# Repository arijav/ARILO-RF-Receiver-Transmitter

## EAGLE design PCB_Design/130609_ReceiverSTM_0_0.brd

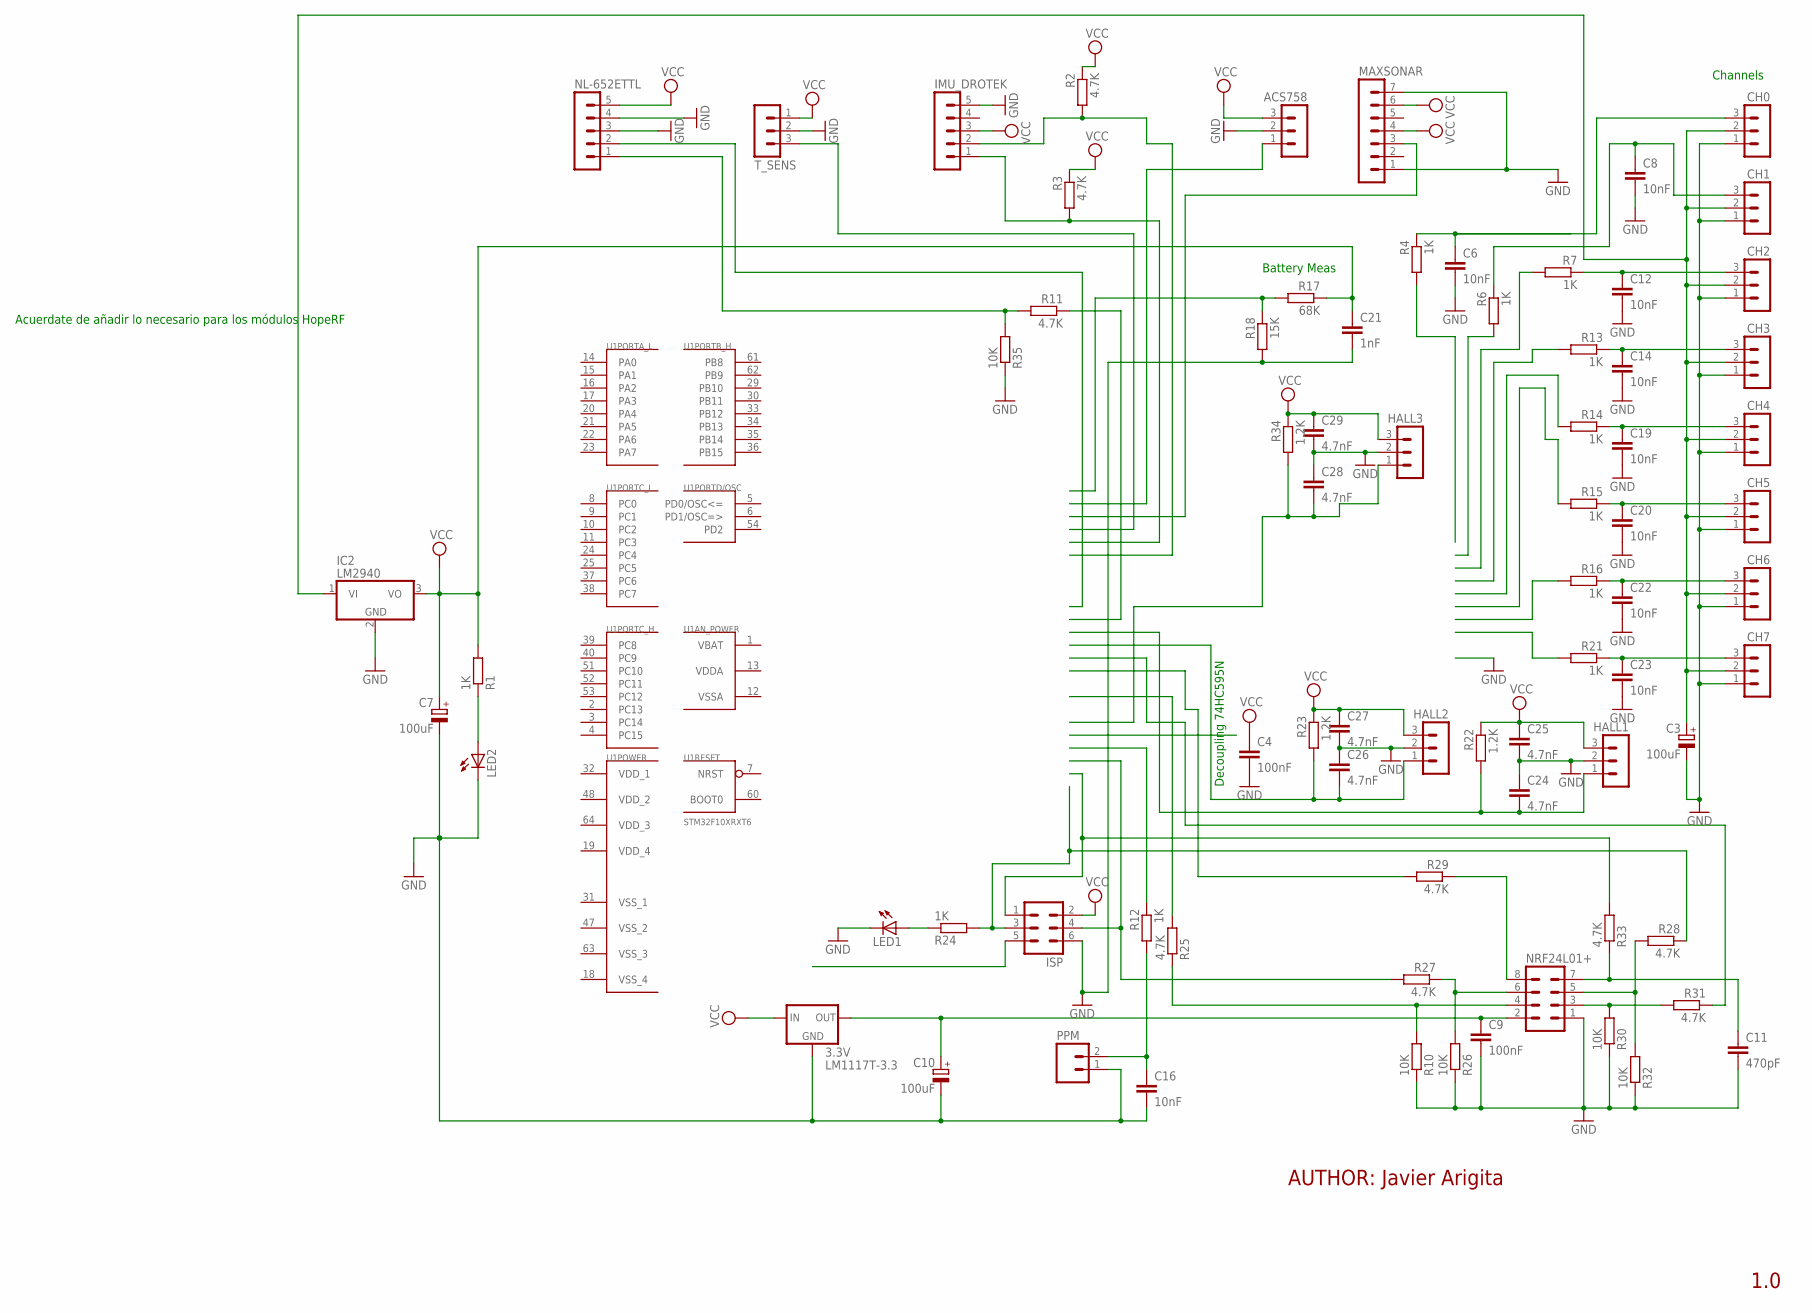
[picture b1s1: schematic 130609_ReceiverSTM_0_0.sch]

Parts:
3.3V: LM1117T-3.3; TO220
ACS758: MA03-1
C3, C7, C10: 100uF; E2,5-6E
C4, C9: 100nF; C050-025X075
C6, C8, C12, C14, C16, C19, C20, C22, C23: 10nF; C025-030X050
C11: 470pF; C025-030X050
C21: 1nF; C050-025X075
C24, C25, C26, C27, C28, C29: 4.7nF; C025-030X050
CH0, CH1, CH2, CH3, CH4, CH5, CH6, CH7: MA03-1
HALL1, HALL2, HALL3: MA03-1
IC2: LM2940; TO220V
IMU_DROTEK: MA05-1
ISP: MA03-2
LED1, LED2: LED5MM
MAXSONAR: MA07-1
NL-652ETTL: MA05-1
NRF24L01+: MA04-2
PPM: M02; 02P
R1, R4, R6, R7, R12, R13, R14, R15, R16, R21, R24: 1K; 0204/7
R2, R3, R11, R25, R27, R28, R29, R31, R33: 4.7K; 0204/7
R10, R26, R30, R32, R35: 10K; 0204/7
R17: 68K; 0204/7
R18: 15K; 0204/7
R22, R23, R34: 1.2K; 0204/7
T_SENS: MA03-1
U1: STM32F10XRXT6; TQFP64

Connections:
GND: 3.3V.1 (GND), ACS758.2, C3.-, C4.2, C6.2, C7.-, C8.2, C9.2, C10.-, C11.2, C12.2, C14.2, C16.2, C19.2, C20.2, C21.2, C22.2, C23.2, C24.1, C25.2, C26.1, C27.2, C28.1, C29.2, CH0.1, CH1.1, CH2.1, CH3.1, CH4.1, CH5.1, CH6.1, CH7.1, HALL1.2, HALL2.2, HALL3.2, IC2.2 (GND), IMU_DROTEK.5, ISP.6, LED1.K (C), LED2.K (C), MAXSONAR.1, MAXSONAR.7, NL-652ETTL.3, NL-652ETTL.4, NRF24L01+.1, PPM.1, R10.1, R18.2, R26.1, R30.1, R32.1, R35.1, T_SENS.2
MAX_BRIDGE: NL-652ETTL.2
unnamed: 3.3V.3 (IN), ACS758.3, C4.1, C7.+, C21.1, C25.1, C27.1, C29.1, HALL1.3, HALL2.3, HALL3.3, IC2.3 (VO), IMU_DROTEK.3, ISP.2, MAXSONAR.4, MAXSONAR.6, NL-652ETTL.5, R1.2, R2.1, R3.1, R17.1, R22.1, R23.1, R34.1, T_SENS.1
unnamed: LED2.A, R1.1
unnamed: IMU_DROTEK.2, R2.2
unnamed: C28.2, HALL3.1, R34.2
unnamed: C24.2, HALL1.1, R22.2
unnamed: 3.3V.2 (OUT), C9.1, C10.+, NRF24L01+.2
unnamed: NRF24L01+.4, R10.2, R25.1
unnamed: NRF24L01+.3, R30.2, R31.2
unnamed: C16.1, PPM.2, R12.2
unnamed: NL-652ETTL.1, R11.2, R35.2
unnamed: IMU_DROTEK.1, R3.2
unnamed: C26.2, HALL2.1, R23.2
unnamed: R17.2, R18.1
unnamed: C3.+, CH0.2, CH1.2, CH2.2, CH3.2, CH4.2, CH5.2, CH6.2, CH7.2, IC2.1 (VI)
unnamed: ISP.3, R24.2, R28.1
unnamed: LED1.A, R24.1
unnamed: ISP.1, R33.2
unnamed: ISP.4, R27.2
unnamed: NRF24L01+.8, R29.1
unnamed: NRF24L01+.6, R26.2, R27.1
unnamed: NRF24L01+.5, R28.2, R32.2
unnamed: C11.1, NRF24L01+.7, R33.1
unnamed: C6.1, CH0.3, R4.1
unnamed: C8.1, CH1.3, R6.1
unnamed: C12.1, CH2.3, R7.1
unnamed: C14.1, CH3.3, R13.1
unnamed: C19.1, CH4.3, R14.1
unnamed: C20.1, CH5.3, R15.1
unnamed: C22.1, CH6.3, R16.1
unnamed: C23.1, CH7.3, R21.1
VBAT: U1.1 (VBAT)
VDDA: U1.13 (VDDA)
VDD_1: U1.32 (VDD_1)
VDD_2: U1.48 (VDD_2)
VDD_3: U1.64 (VDD_3)
VDD_4: U1.19 (VDD_4)
VSSA: U1.12 (VSSA)
VSS_1: U1.31 (VSS_1)
VSS_2: U1.47 (VSS_2)
VSS_3: U1.63 (VSS_3)
VSS_4: U1.18 (VSS_4)

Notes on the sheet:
Battery Meas
Acuerdate de añadir lo necesario para los módulos HopeRF
AUTHOR: Javier Arigita
1.0
Channels
Decoupling 74HC595N

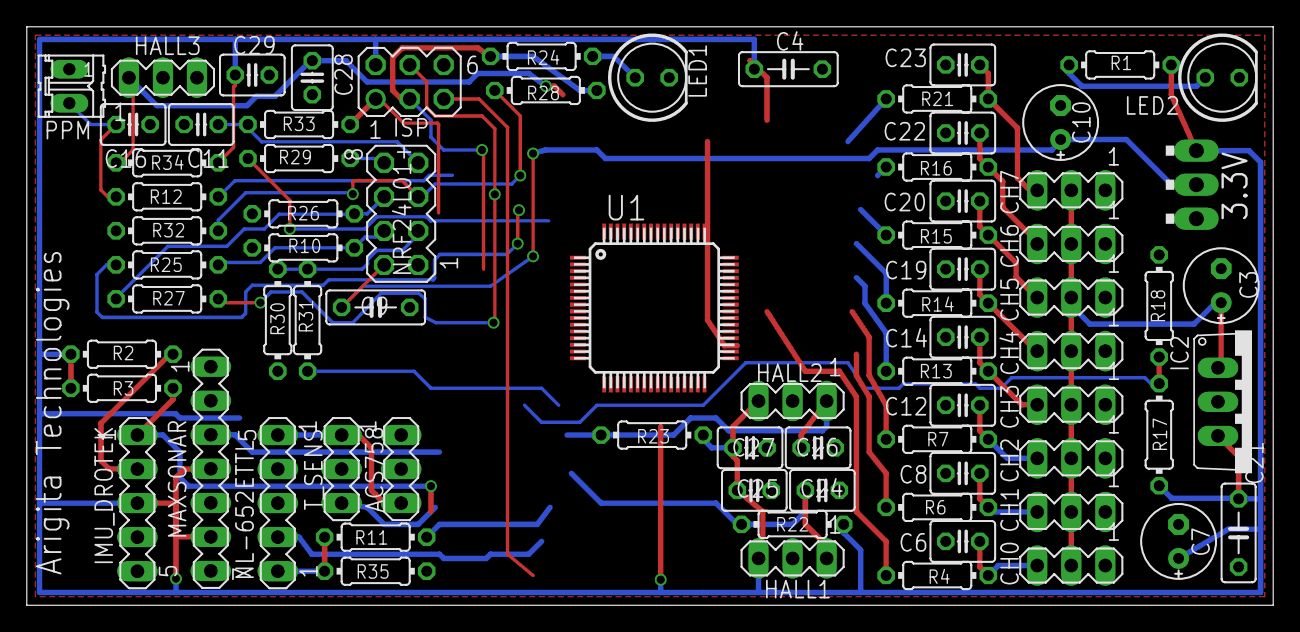
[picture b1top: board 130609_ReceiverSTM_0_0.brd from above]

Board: 2 copper layers, 93.0 x 43.2 mm, 76 parts (0 on the bottom side), 31 nets.

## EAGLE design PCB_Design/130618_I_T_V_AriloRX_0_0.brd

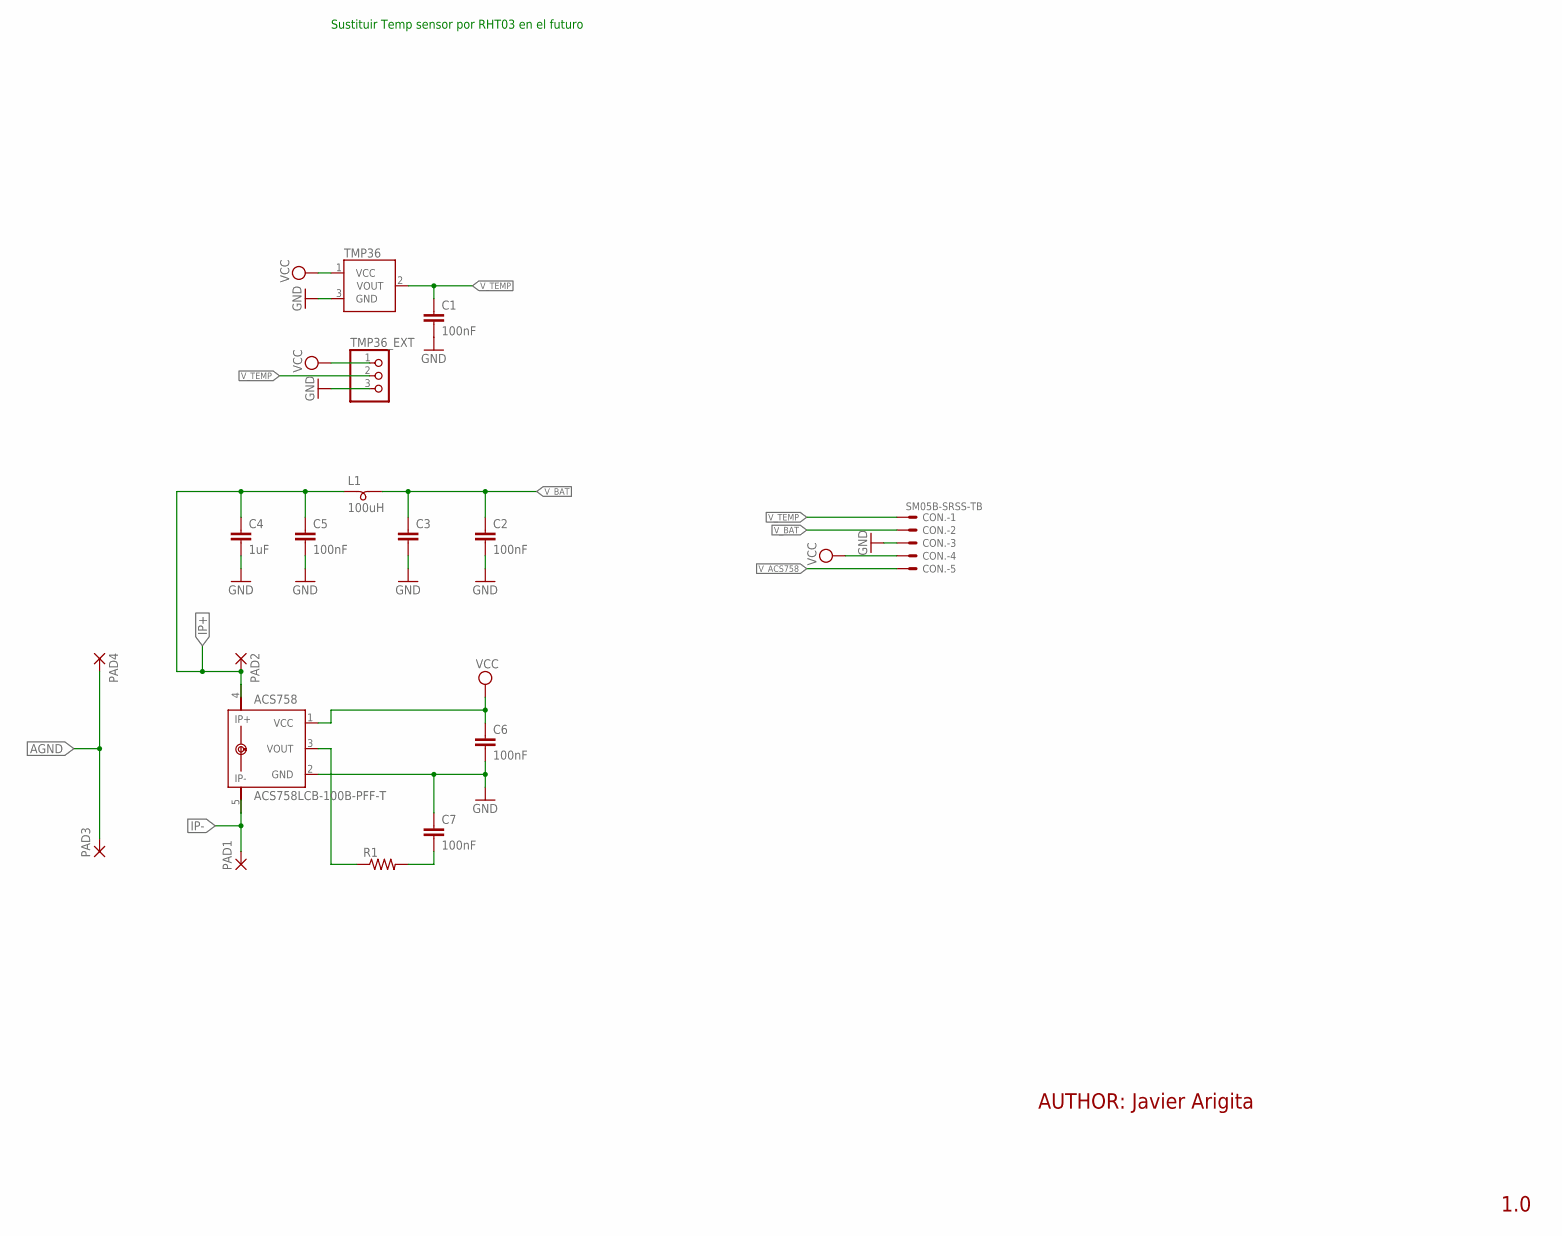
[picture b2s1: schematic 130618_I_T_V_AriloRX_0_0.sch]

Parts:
ACS758: ACS758LCB-100B-PFF-T; CB-PFF
C1, C2, C5, C6, C7: 100nF; C0805
C3: C-EUC3216; C3216
C4: 1uF; C3216
CON.: SM05B-SRSS-TB
L1: 100uH; SM-B5
PAD1, PAD2, PAD3, PAD4: SMD5; SMD2,54-5,08
R1: RESISTOR0805; R0805
TMP36: TMP36GT9; TO-92
TMP36_EXT: PINHD-1X3; 1X03

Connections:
AGND: PAD3.1, PAD4.1
GND: ACS758.2 (GND), C1.2, C2.2, C3.2, C4.2, C5.2, C6.2, C7.1, CON..3, TMP36.3 (GND), TMP36_EXT.3
IP+: ACS758.4 (IP+), ACS758.IP+1, C4.1, C5.1, L1.1, PAD2.1
IP-: ACS758.5 (IP-), ACS758.IP-1, PAD1.1
unnamed: C7.2, R1.2
unnamed: ACS758.3 (VOUT), R1.1
VCC: ACS758.1 (VCC), C6.1, CON..4, TMP36.1 (VCC), TMP36_EXT.1
V_ACS758: CON..5
V_BAT: C2.1, C3.1, CON..2, L1.2
V_TEMP: C1.1, CON..1, TMP36.2 (VOUT), TMP36_EXT.2

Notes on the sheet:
AUTHOR: Javier Arigita
1.0
Sustituir Temp sensor por RHT03 en el futuro

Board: 2 copper layers, 17 parts (0 on the bottom side), 9 nets, no tracks yet.

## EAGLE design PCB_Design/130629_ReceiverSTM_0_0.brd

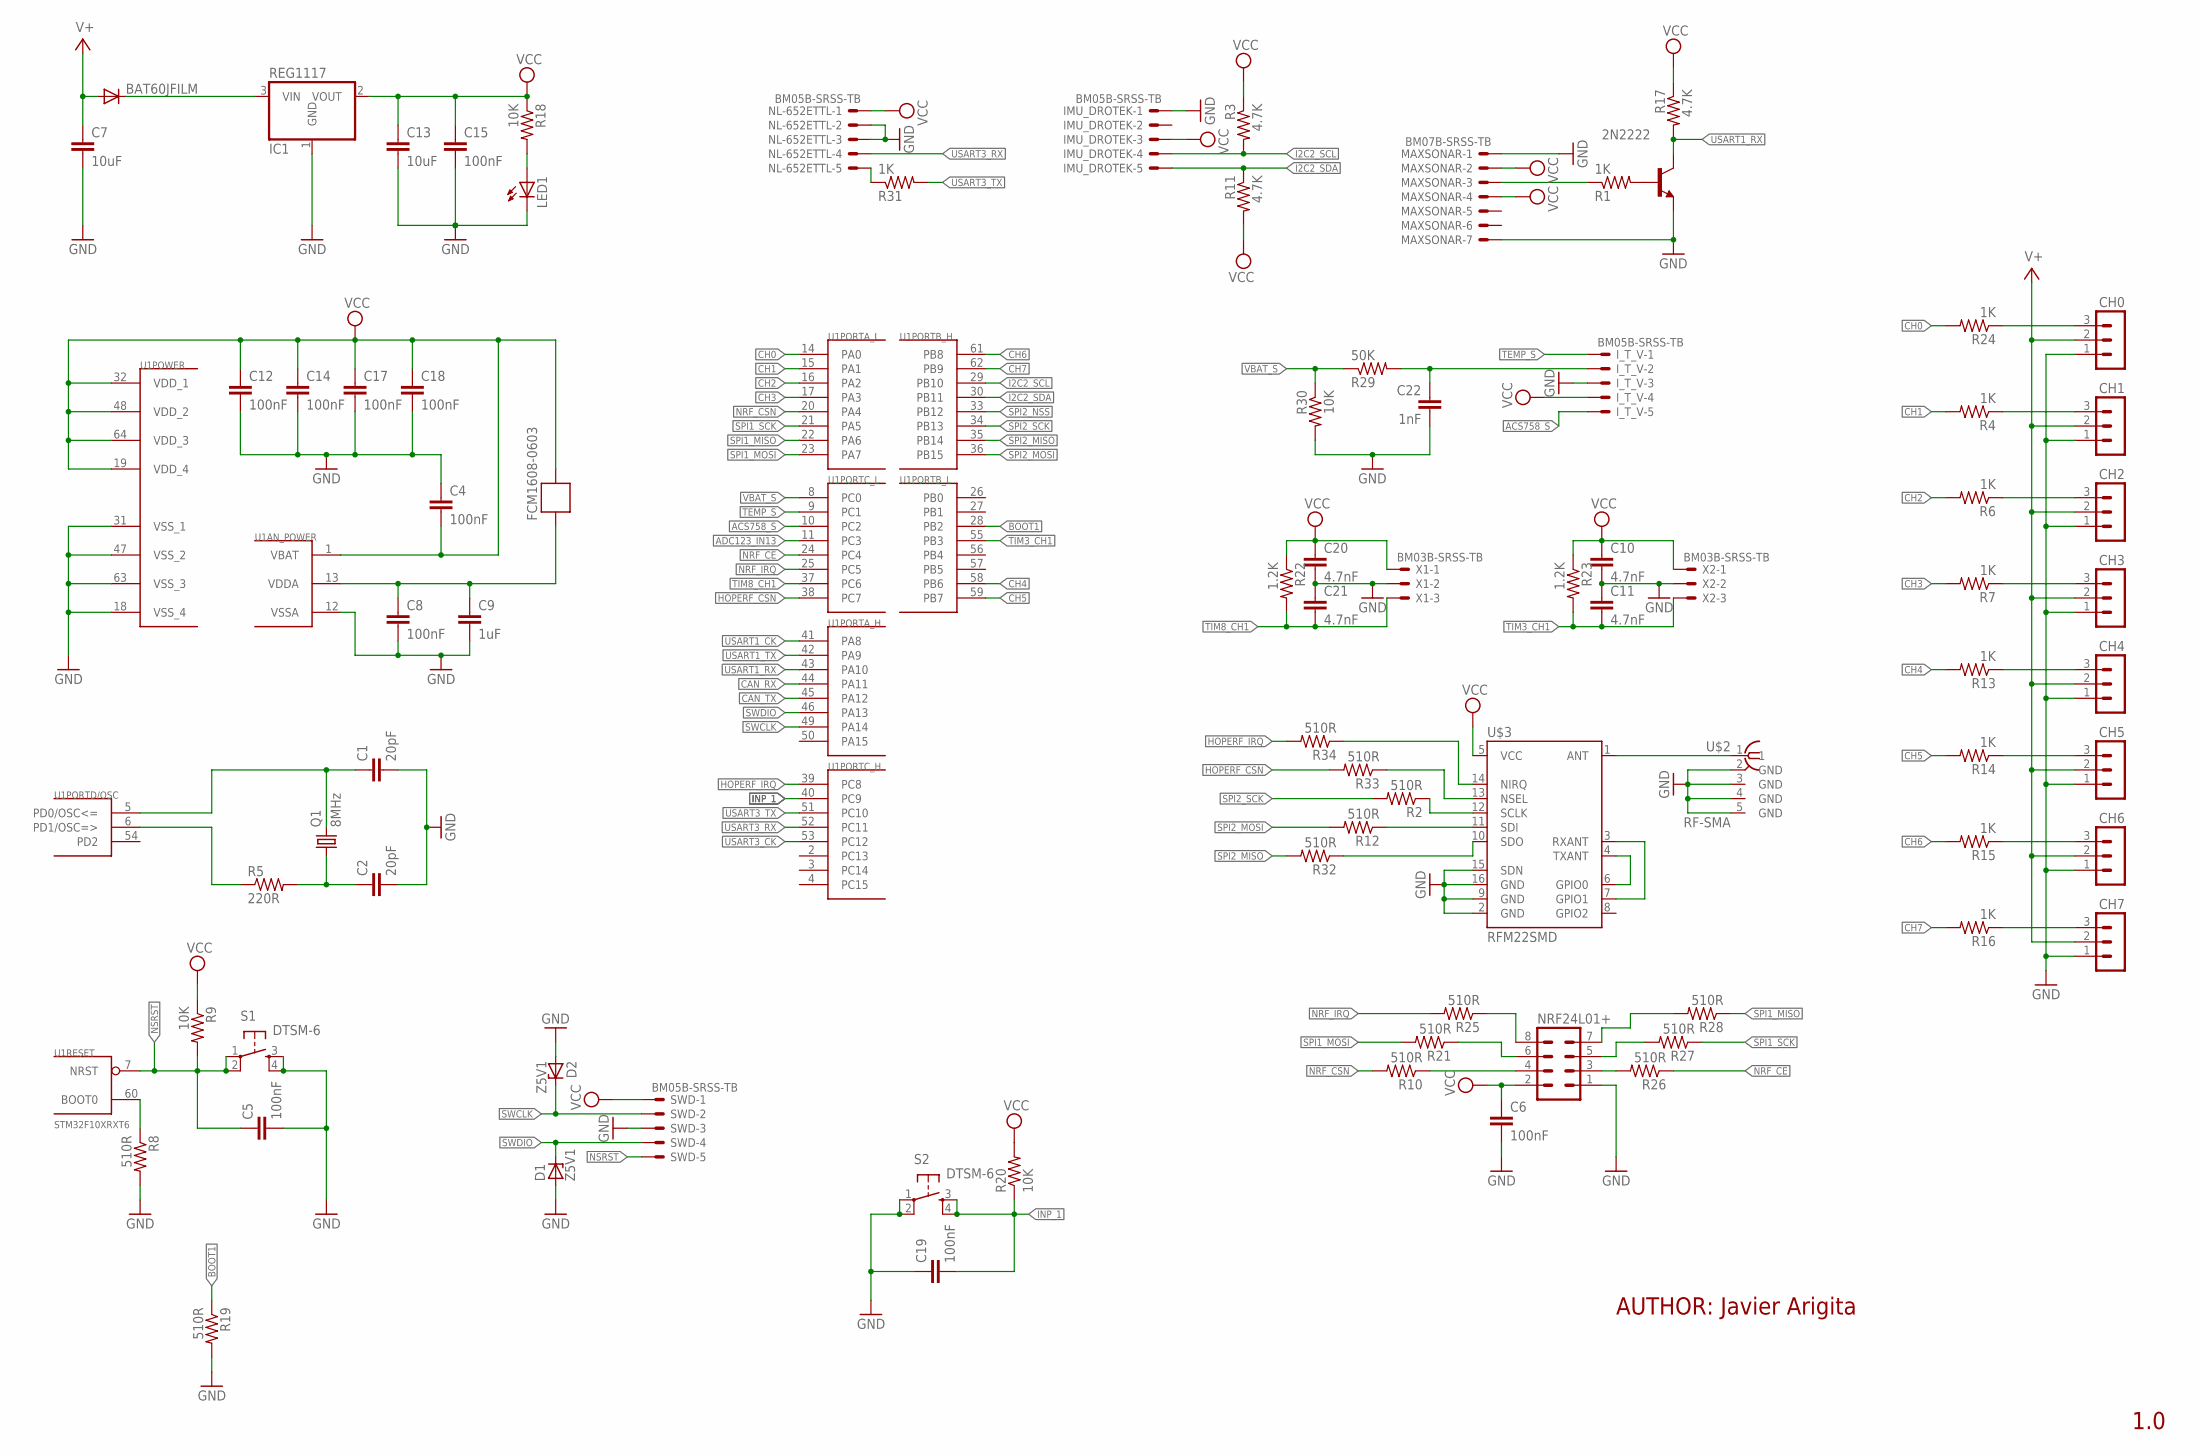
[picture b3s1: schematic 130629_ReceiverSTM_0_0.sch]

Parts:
2N2222: MMBT2222ALT1-NPN-SOT23-BEC; SOT23-BEC
BAT60JFILM: DIODE-SOD323-R; SOD323-R
C1, C2: 20pF; C0805
C4, C5, C6, C8, C12, C14, C15, C17, C18, C19: 100nF; C0805
C7, C13: 10uF; C3216
C9: 1uF; C3216
C10, C11, C20, C21: 4.7nF; C0805
C22: 1nF; C0805
CH0, CH1, CH2, CH3, CH4, CH5, CH6, CH7: MA03-1
D1, D2: Z5V1; SOD80C
FCM1608-0603: FERRITE-BEAD; R0603
IC1: REG1117; SOT223
IMU_DROTEK: BM05B-SRSS-TB
I_T_V: BM05B-SRSS-TB
LED1: LED0805; CHIPLED_0805
MAXSONAR: BM07B-SRSS-TB
NL-652ETTL: BM05B-SRSS-TB
NRF24L01+: MA04-2
Q1: 8MHz; SM49
R1, R4, R6, R7, R13, R14, R15, R16, R24, R31: 1K; R0805
R2, R8, R10, R12, R19, R21, R25, R26, R27, R28, R32, R33, R34: 510R; R0805
R3, R11, R17: 4.7K; R0805
R5: 220R; R0805
R9, R18, R20, R30: 10K; R0805
R22, R23: 1.2K; R0805
R29: 50K; R0805
S1, S2: DTSM-6
SWD: BM05B-SRSS-TB
U1: STM32F10XRXT6; TQFP64
U$2: RF-SMA; BU-SMA-H
U$3: RFM22SMD; RFM22-XXX-S2
X1, X2: BM03B-SRSS-TB

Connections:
ACS758_S: I_T_V.5, U1.10 (PC2)
ADC123_IN13: U1.11 (PC3)
BOOT1: R19.1, U1.28 (PB2)
CAN_RX: U1.44 (PA11)
CAN_TX: U1.45 (PA12)
CH0: R24.2, U1.14 (PA0)
CH1: R4.2, U1.15 (PA1)
CH2: R6.2, U1.16 (PA2)
CH3: R7.2, U1.17 (PA3)
CH4: R13.2, U1.58 (PB6)
CH5: R14.2, U1.59 (PB7)
CH6: R15.2, U1.61 (PB8)
CH7: R16.2, U1.62 (PB9)
GND: 2N2222.E, C1.2, C2.2, C4.1, C5.2, C6.2, C7.2, C8.2, C9.2, C10.2, C11.1, C12.2, C13.2, C14.2, C15.2, C17.2, C18.2, C19.1, C20.2, C21.1, C22.2, CH0.1, CH1.1, CH2.1, CH3.1, CH4.1, CH5.1, CH6.1, CH7.1, D1.A, D2.A, IC1.1 (GND), IMU_DROTEK.1, I_T_V.3, LED1.C, MAXSONAR.1, MAXSONAR.7, NL-652ETTL.2, NL-652ETTL.3, NRF24L01+.1, R8.2, R19.2, R30.2, S1.3, S1.4, S2.1, S2.2, SWD.3, U1.12 (VSSA), U1.18 (VSS_4), U1.31 (VSS_1), U1.47 (VSS_2), U1.63 (VSS_3), U$2.2 (GND), U$2.3 (GND), U$2.4 (GND), U$2.5 (GND), U$3.2 (GND), U$3.9 (GND), U$3.15 (SDN), U$3.16 (GND), X1.2, X2.2
HOPERF_CSN: R33.1, R33.2, U1.38 (PC7), U$3.13 (NSEL)
HOPERF_IRQ: R34.2, U1.39 (PC8)
I2C2_SCL: IMU_DROTEK.4, R3.2, U1.29 (PB10)
I2C2_SDA: IMU_DROTEK.5, R11.1, U1.30 (PB11)
INP_1: C19.2, R20.1, S2.3, S2.4, U1.40 (PC9)
unnamed: C1.1, Q1.2, U1.5 (PD0/OSC<=)
unnamed: R5.1, U1.6 (PD1/OSC=>)
unnamed: C2.1, Q1.1, R5.2
unnamed: R8.1, U1.60 (BOOT0)
unnamed: U$3.3 (RXANT), U$3.7 (GPIO1)
unnamed: R2.1, U$3.12 (SCLK)
unnamed: R12.1, U$3.11 (SDI)
unnamed: CH0.3, R24.1
unnamed: LED1.A, R18.2
unnamed: NL-652ETTL.5, R31.1
unnamed: R32.1, U$3.10 (SDO)
unnamed: BAT60JFILM.C, IC1.3 (VIN)
unnamed: MAXSONAR.3, R1.1
unnamed: C22.1, I_T_V.2, R29.2
unnamed: 2N2222.B, R1.2
unnamed: C8.1, C9.1, FCM1608-0603.2, U1.13 (VDDA)
unnamed: NRF24L01+.4, R10.1
unnamed: NRF24L01+.3, R26.2
unnamed: CH2.3, R6.1
unnamed: R34.1, U$3.14 (NIRQ)
unnamed: CH4.3, R13.1
unnamed: CH3.3, R7.1
unnamed: CH6.3, R15.1
unnamed: CH5.3, R14.1
unnamed: CH7.3, R16.1
unnamed: NRF24L01+.5, R27.2
unnamed: NRF24L01+.6, R21.1
unnamed: NRF24L01+.8, R25.1
unnamed: NRF24L01+.7, R28.2
unnamed: CH1.3, R4.1
NRF_CE: R26.1, U1.24 (PC4)
NRF_CSN: R10.2, U1.20 (PA4)
NRF_IRQ: R25.2, U1.25 (PC5)
NSRST: C5.1, R9.2, S1.1, S1.2, SWD.5, U1.7 (NRST)
SPI1_MISO: R28.1, U1.22 (PA6)
SPI1_MOSI: R21.2, U1.23 (PA7)
SPI1_SCK: R27.1, U1.21 (PA5)
SPI2_MISO: R32.2, U1.35 (PB14)
SPI2_MOSI: R12.2, U1.36 (PB15)
SPI2_NSS: U1.33 (PB12)
SPI2_SCK: R2.2, U1.34 (PB13)
SWCLK: D2.C, SWD.2, U1.49 (PA14)
SWDIO: D1.C, SWD.4, U1.46 (PA13)
TEMP_S: I_T_V.1, U1.9 (PC1)
TIM3_CH1: C11.2, R23.2, U1.55 (PB3), X2.3
TIM8_CH1: C21.2, R22.2, U1.37 (PC6), X1.3
USART1_CK: U1.41 (PA8)
USART1_RX: 2N2222.C, R17.2, U1.43 (PA10)
USART1_TX: U1.42 (PA9)
USART3_CK: U1.53 (PC12)
USART3_RX: NL-652ETTL.4, U1.52 (PC11)
USART3_TX: R31.2, U1.51 (PC10)
V+: BAT60JFILM.A, C7.1, CH0.2, CH1.2, CH2.2, CH3.2, CH4.2, CH5.2, CH6.2, CH7.2
VBAT_S: R29.1, R30.1, U1.8 (PC0)
VCC: C4.2, C6.1, C10.1, C12.1, C13.1, C14.1, C15.1, C17.1, C18.1, C20.1, FCM1608-0603.1, IC1.2 (VOUT), IMU_DROTEK.3, I_T_V.4, MAXSONAR.2, MAXSONAR.4, NL-652ETTL.1, NRF24L01+.2, R3.1, R9.1, R11.2, R17.1, R18.1, R20.2, R22.1, R23.1, SWD.1, U1.1 (VBAT), U1.19 (VDD_4), U1.32 (VDD_1), U1.48 (VDD_2), U1.64 (VDD_3), U$3.5 (VCC), X1.1, X2.1

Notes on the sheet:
AUTHOR: Javier Arigita
1.0

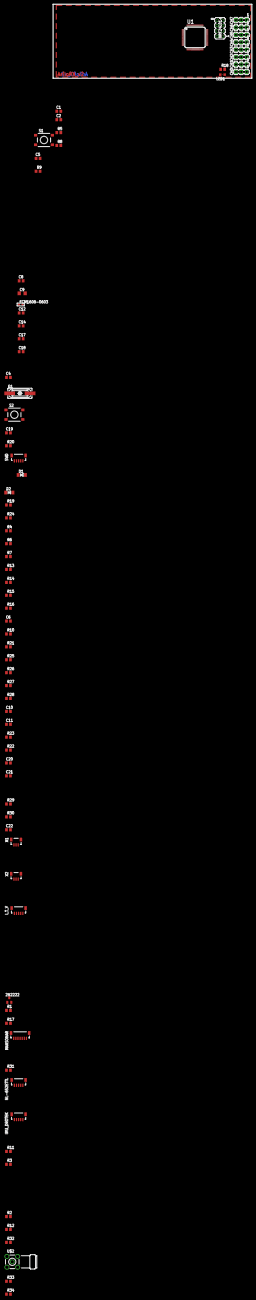
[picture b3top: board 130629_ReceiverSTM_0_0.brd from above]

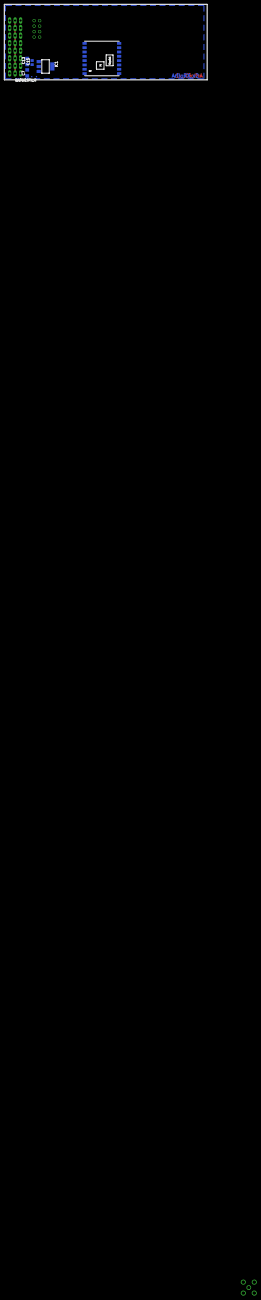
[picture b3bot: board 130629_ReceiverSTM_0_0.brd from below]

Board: 2 copper layers, 94.0 x 35.0 mm, 83 parts (6 on the bottom side), 67 nets.

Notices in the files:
parts and their libraries:
SparkFun-Sensors: Licensing: CC v3.0 Share-Alike You are welcome to use this library for commercial purposes.
